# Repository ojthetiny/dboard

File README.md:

# unscuffed XYZTKL daughterboard
 less scuffed xyztkl daughterboard using m2 screws instead of m3, added ESD protection and a fuse which were missing from the original for some reason unknown to anyone but the designer

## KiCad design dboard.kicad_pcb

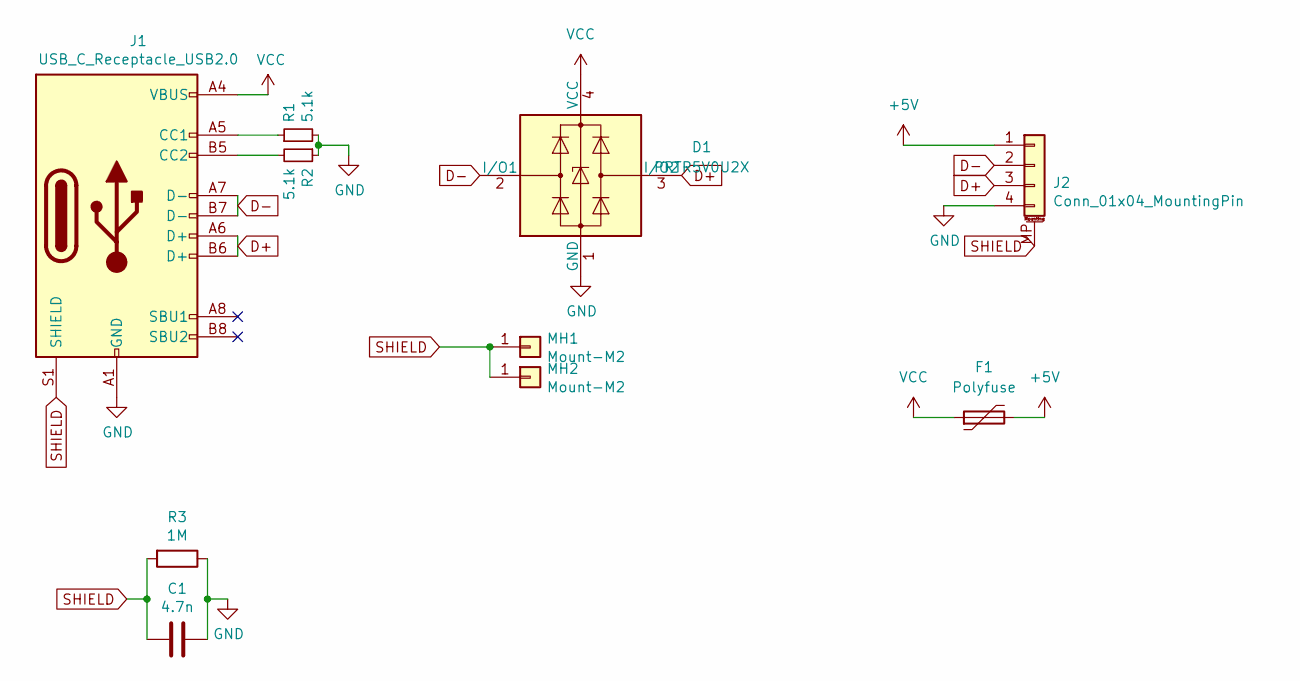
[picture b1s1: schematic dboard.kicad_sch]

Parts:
C1: 4.7n; C_0603_1608Metric; LCSC C53987
D1: PRTR5V0U2X; SOT-143
F1: Polyfuse; Fuse_0805_2012Metric
J1: USB_C_Receptacle_USB2.0; USB_C_Receptacle_HRO_TYPE-C-31-M-12; LCSC C165948
J2: Conn_01x04_MountingPin; JST_SH_SM04B-SRSS-TB_1x04-1MP_P1.00mm_Horizontal; LCSC C160404
MH1, MH2: Mount-M2; MountingHole_2.2mm_M2_Pad_Via
R1, R2: 5.1k; R_0603_1608Metric; LCSC C23186
R3: 1M; R_0805_2012Metric; LCSC C17514

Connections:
+5V: F1.2, J2.1
D+: D1.3 (I/O2), J1.A6 (D+), J1.B6 (D+), J2.3
D-: D1.2 (I/O1), J1.A7 (D-), J1.B7 (D-), J2.2
GND: C1.1, D1.1 (GND), J1.A1 (GND), J1.A12 (GND), J1.B1 (GND), J1.B12 (GND), J2.4, R1.2, R2.1, R3.1
unnamed: J1.A5 (CC1), R1.1
unnamed: J1.B5 (CC2), R2.2
SHIELD: C1.2, J1.S1 (SHIELD), J2.MP (MountPin), MH1.1, MH2.1, R3.2
VCC: D1.4 (VCC), F1.1, J1.A4 (VBUS), J1.A9 (VBUS), J1.B4 (VBUS), J1.B9 (VBUS)

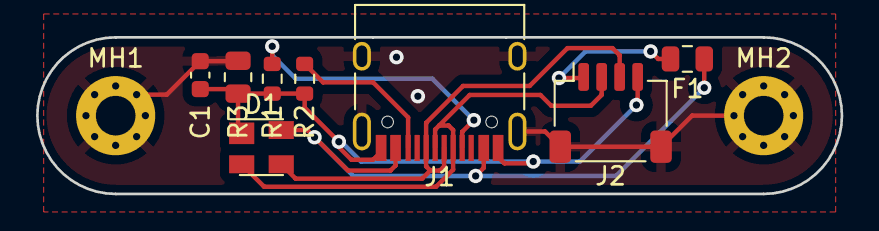
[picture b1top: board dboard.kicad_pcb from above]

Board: 2 copper layers, 44.7 x 8.7 mm, 10 parts (0 on the bottom side), 8 nets.

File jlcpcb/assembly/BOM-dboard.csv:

Comment,Designator,Footprint,LCSC
PRTR5V0U2X,D1,SOT-143,C12333
Conn_01x04_MountingPin,J2,JST_SH_SM04B-SRSS-TB_1x04-1MP_P1.00mm_Horizontal,C160404
USB_C_Receptacle_USB2.0,J1,USB_C_Receptacle_HRO_TYPE-C-31-M-12,C165948
1M,R3,R_0805_2012Metric,C17514
5.1k,"R1,R2",R_0603_1608Metric,C23186
4.7n,C1,C_0603_1608Metric,C53987
Polyfuse,F1,Fuse_0805_2012Metric,C883103
Mount-M2,MH2,MountingHole_2.2mm_M2_Pad_Via,
Mount-M2,MH1,MountingHole_2.2mm_M2_Pad_Via,

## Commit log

2022-01-25 fixed pinout
    made pinout udb compatible
